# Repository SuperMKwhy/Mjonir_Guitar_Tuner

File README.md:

# Mjonir — Automatic Guitar Tuner

A handheld automatic guitar tuner built on an ESP32. A MEMS microphone listens to
the plucked string, an FFT finds its pitch, and a DC motor turns the tuning peg
until the string is in tune. An SSD1306 OLED and a 4-button D-pad provide the UI.

> **Status: work in progress.** The hardware is still being developed, so the
> firmware is incomplete and has not been fully tested on the final board.

## Features

- Pitch detection with a 2048-point FFT (ESP-DSP) on the INMP441 I2S microphone
- Motor drive through a DRV8833, with speed proportional to the tuning error
- Tuning presets: **Default** (E A D G B E), **All Flat** (Eb), and **Custom**
  (choose any note for each string)
- **Manual** mode (you pick the string) and **Auto** mode (detects the closest string)
- On-screen tuning meter showing the target note, its neighbours, and a ±2% in-tune window
- Battery level indicator

## Repository layout

```
firmware/   ESP-IDF project (C++)
  main/                 app entry point and page stack loop
  components/tunerLib/  I2S microphone driver, FIR filter + downsampling, FFT pitch detection
  components/control/   DRV8833 motor control (LEDC PWM)
  components/page/      UI pages: menu, tuning presets, custom tuning, tuner
  components/display/   SSD1306 helpers
  components/system/    D-pad input, cursor, battery ADC, note/frequency utilities
hardware/   KiCad 9 project: main PCB, D-pad PCB, BOM, PDFs, STEP models
cad/        Mechanical enclosure model (SolidWorks; to be added)
```

## Hardware

| Part | Notes |
|---|---|
| ESP32-WROOM-32 | Main MCU |
| INMP441 | I2S MEMS microphone |
| DRV8833 module | Motor driver for the peg winder |
| SSD1306 OLED 128×64 | I2C display |
| 4× tactile switch | D-pad on a separate PCB |
| YB-8 module, battery, power switch, buzzer | See `hardware/2. Project Tuner.csv` for the full BOM |

### Pin map

| Function | GPIO |
|---|---|
| OLED SDA / SCL | 21 / 22 |
| I2S WS / SCK / SD | 12 / 14 / 13 |
| Motor AIN1 / AIN2 | 18 / 19 |
| D-pad Up / Right (OK) / Down / Left (Back) | 25 / 26 / 32 / 33 |
| Battery sense (ADC1_CH7) | 35 |

## Building the firmware

Requires **ESP-IDF v5.1.x**. The `esp-dsp` and `ssd1306` components are
downloaded automatically by the IDF component manager.

```bash
. ~/esp/esp-idf/export.sh
cd firmware
idf.py set-target esp32   # first time only
idf.py build
idf.py -p /dev/ttyUSB0 flash monitor
```

> If you use Anaconda, its `python3` can conflict with ESP-IDF's Python
> environment. Put the system Python first: `export PATH=/usr/bin:$PATH` before
> sourcing `export.sh`.

## Controls

| Button | Action |
|---|---|
| Up / Down | Move the cursor, or change the value while editing |
| Right | OK / select |
| Left | Back / cancel |

## Known limitations / TODO

- Bass tuning is listed in the menu but not implemented yet
- Noise calibration is disabled (`calibration_time = 0`)
- Pitch resolution is about 1 Hz per FFT bin with no interpolation, which is coarse
  for low strings
- Uses legacy ESP-IDF I2S, ADC and SSD1306 drivers (deprecated in IDF 5.x)
- The buzzer is on the PCB but not used by the firmware yet
- Mechanical CAD model not yet in the repo

> ⚠️ When testing, keep the motor disconnected from the peg until you have
> confirmed the direction of rotation, so it cannot over-tighten a string.

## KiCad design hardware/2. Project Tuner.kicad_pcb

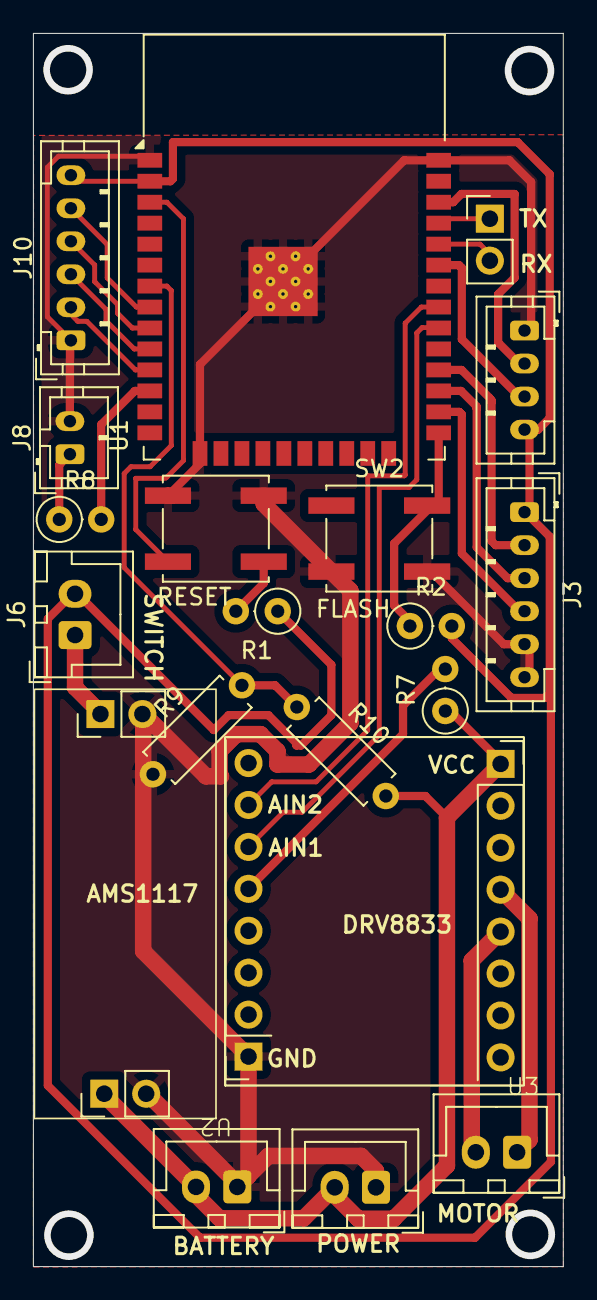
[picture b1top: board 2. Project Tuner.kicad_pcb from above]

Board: 2 copper layers, 32.1 x 74.7 mm, 20 parts (0 on the bottom side), 25 nets.

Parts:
J1: BATTERY; JST_XH_B2B-XH-A_1x02_P2.50mm_Vertical
J2: Flasher; PinHeader_1x02_P2.54mm_Vertical
J3: INMP441 Connection; JST_PH_B6B-PH-K_1x06_P2.00mm_Vertical
J4: POWER; JST_XH_B2B-XH-A_1x02_P2.50mm_Vertical
J5: Motor; JST_XH_B2B-XH-A_1x02_P2.50mm_Vertical
J6: ON/OFF Switch; JST_XH_B2B-XH-A_1x02_P2.50mm_Vertical
J7: ssd1306; JST_PH_B4B-PH-K_1x04_P2.00mm_Vertical
J8: Buzzer; JST_PH_B2B-PH-K_1x02_P2.00mm_Vertical
J10: D-Pad-Out; JST_PH_B6B-PH-K_1x06_P2.00mm_Vertical
R1, R2, R7: 10k; R_Axial_DIN0207_L6.3mm_D2.5mm_P2.54mm_Vertical
R8: 100; R_Axial_DIN0207_L6.3mm_D2.5mm_P2.54mm_Vertical
R9: 10k; R_Axial_DIN0207_L6.3mm_D2.5mm_P7.62mm_Horizontal
R10: 20k; R_Axial_DIN0207_L6.3mm_D2.5mm_P7.62mm_Horizontal
RESET: RESET; SW_Push_1P1T_NO_CK_KSC6xxJ
SW2: FLASH; SW_Push_1P1T_NO_CK_KSC6xxJ
U1: ESP32-WROOM-32
U2: YB-8
U3: DRV8833 Module

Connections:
/AIN1: U1.30 (IO18), U3.6 (BO2)
/AIN2: U1.31 (IO19), U3.7 (BO1)
/AO1: J5.1, U3.4 (AO1)
/AO2: J5.2, U3.5 (AO2)
/Buzzer: R8.2, U1.12 (IO27)
/DOWN-Board: J10.5, U1.8 (IO32)
/LEFT-Board: J10.4, U1.9 (IO33)
/PERCENT: R9.2, R10.1, U1.7 (IO35)
/RIGHT-Board: J10.2, U1.11 (IO26)
/RX_Socket: J2.2, U1.34 (RXD0/IO3)
/SCK: J3.4, U1.26 (IO4)
/SCL: J7.2, U1.36 (IO22)
/SD: J3.2, U1.28 (IO17)
/SDA: J7.3, U1.33 (IO21)
/STBY: R7.2, U3.5 (AO2)
/TX_Socket: J2.1, U1.35 (TXD0/IO1)
/UP-Board: J10.3, U1.10 (IO25)
/V_PRE: J6.1, U2.1 (V_IN)
/WS: J3.3, U1.27 (IO16)
GND: J1.1, J3.5, J3.6, J4.1, J7.1, J8.2, J10.1, R9.1, RESET.1, SW2.1, U1.1 (GND), U1.15 (GND), U1.38 (GND), U1.39 (GND), U2.2 (GND), U3.1 (VM)
unnamed: J8.1, R8.1
unnamed: R1.2, RESET.2, U1.3 (EN)
unnamed: R2.1, SW2.2, U1.25 (IO0)
VCC: J1.2, J4.2, R7.1, R10.2, U2.1 (V_IN), U3.1 (VM)
VDD: J3.1, J6.2, J7.4, J10.6, R1.1, R2.2, U1.2 (VDD)

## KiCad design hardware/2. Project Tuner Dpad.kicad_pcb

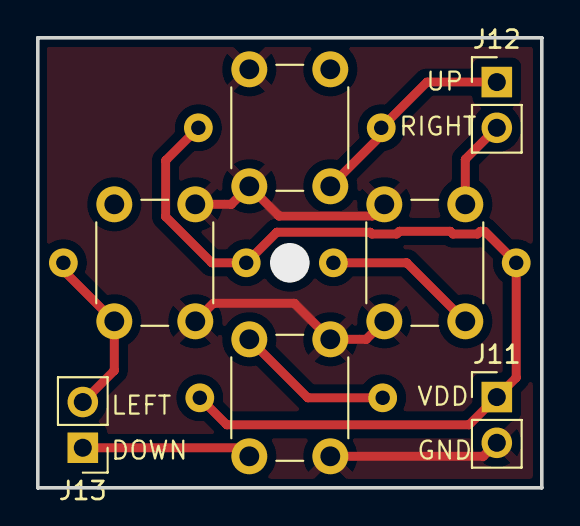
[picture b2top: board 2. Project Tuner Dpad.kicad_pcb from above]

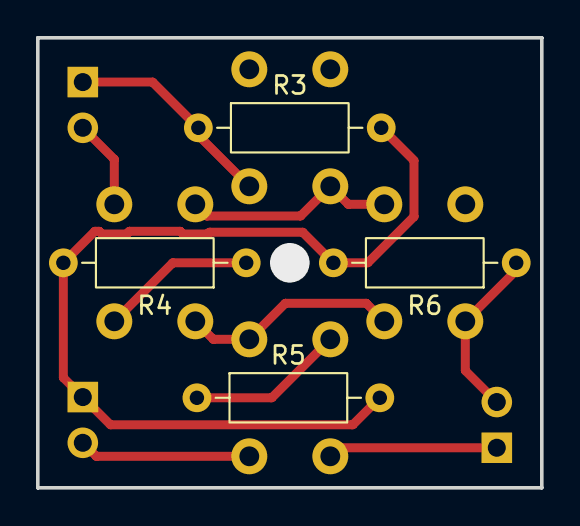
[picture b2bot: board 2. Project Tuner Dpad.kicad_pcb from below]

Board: 2 copper layers, 28.0 x 25.0 mm, 11 parts (4 on the bottom side), 6 nets.

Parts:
J11: D-Pad-PWR; PinHeader_1x02_P2.54mm_Vertical
J12: D-Pad-UR; PinHeader_1x02_P2.54mm_Vertical
J13: D-Pad-LD; PinHeader_1x02_P2.54mm_Vertical
R3, R4, R5, R6: 10k; R_Axial_DIN0207_L6.3mm_D2.5mm_P10.16mm_Horizontal
SW3: UP; SW_PUSH_6mm_H7.3mm
SW4: RIGHT; SW_PUSH_6mm_H7.3mm
SW5: DOWN; SW_PUSH_6mm_H7.3mm
SW6: LEFT; SW_PUSH_6mm_H7.3mm

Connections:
/DOWN: J13.1, R5.1, SW5.1
/GND-D-Pad: J11.2, SW3.2, SW4.2, SW5.2, SW6.2
/LEFT: J13.2, R6.1, SW6.1
/RIGHT: J12.2, R4.1, SW4.1
/UP: J12.1, R3.1, SW3.1
/VDD-D-Pad: J11.1, R3.2, R4.2, R5.2, R6.2

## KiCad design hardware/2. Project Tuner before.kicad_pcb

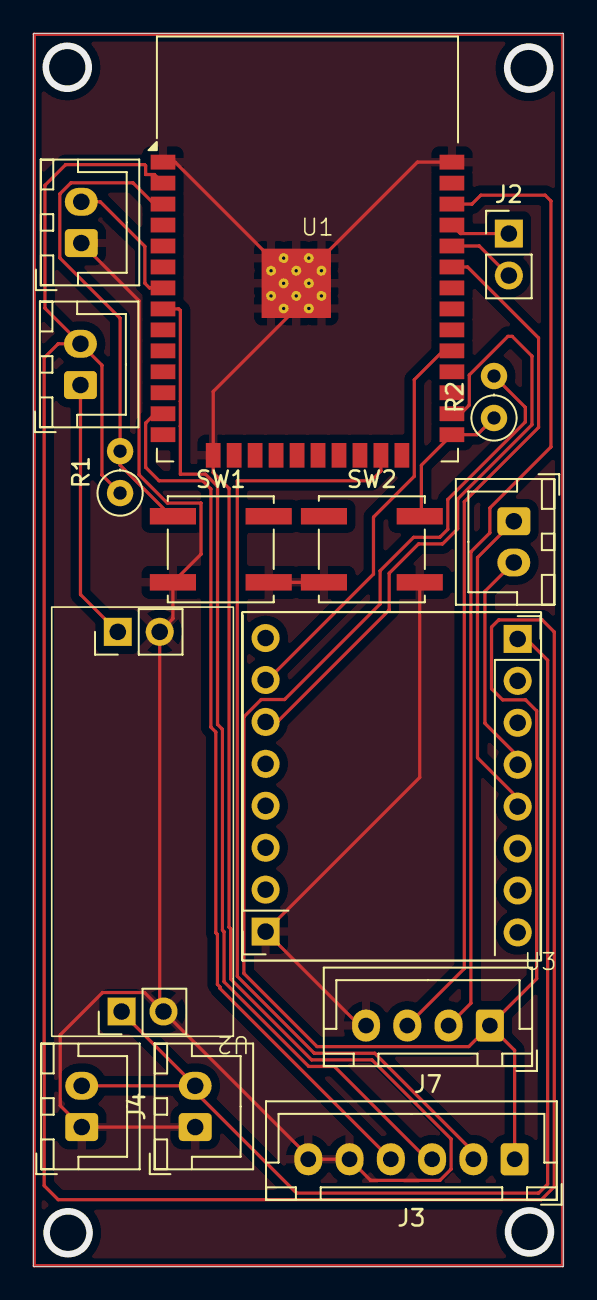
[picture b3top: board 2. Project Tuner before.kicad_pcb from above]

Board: 2 copper layers, 32.1 x 74.7 mm, 15 parts (0 on the bottom side), 16 nets.

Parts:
J1: BATTERY; JST_XH_B2B-XH-A_1x02_P2.50mm_Vertical
J2: Flasher; PinHeader_1x02_P2.54mm_Vertical
J3: INMP441 Connection; JST_XH_B6B-XH-A_1x06_P2.50mm_Vertical
J4: POWER; JST_XH_B2B-XH-A_1x02_P2.50mm_Vertical
J5: Motor; JST_XH_B2B-XH-A_1x02_P2.50mm_Vertical
J6: ON/OFF Switch; JST_XH_B2B-XH-A_1x02_P2.50mm_Vertical
J7: ssd1306; JST_XH_B4B-XH-A_1x04_P2.50mm_Vertical
J8: Buzzer; JST_XH_B2B-XH-A_1x02_P2.50mm_Vertical
R1, R2: 10k; R_Axial_DIN0207_L6.3mm_D2.5mm_P2.54mm_Vertical
SW1: RESET; SW_Push_1P1T_NO_CK_KSC6xxJ
SW2: FLASH; SW_Push_1P1T_NO_CK_KSC6xxJ
U1: ESP32-WROOM-32; ESP-WROOM-32 Edited
U2: YB-8
U3: DRV8833 Module

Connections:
/AIN2: U1.29 (IO5), U3.7 (BO1)
/RX_Socket: J2.2, U1.34 (RXD0/IO3)
/SCK: J3.4, U1.13 (IO14)
/SCL: J7.2, U1.36 (IO22)
/SD: J3.3, U1.8 (IO32)
/SDA: J7.3, U1.33 (IO21)
/TX_Socket: J2.1, U1.35 (TXD0/IO1)
/WS: J3.2, U1.23 (IO15)
GND: J1.1, J3.5, J3.6, J4.1, J7.4, J8.1, SW1.1, SW2.1, U1.1 (GND), U1.15 (GND), U1.38 (GND), U1.39 (GND), U2.2 (GND), U3.1 (VM)
unnamed: J5.1, U3.5 (AO2)
unnamed: J5.2, U3.4 (AO1)
unnamed: J8.2, U1.7 (IO35)
unnamed: R1.2, SW1.2, U1.3 (EN)
unnamed: R2.1, SW2.2, U1.25 (IO0)
VCC: J1.2, J4.2, U2.1 (V_IN), U3.1 (VM)
VDD: J3.1, J6.1, J6.2, J7.1, R1.1, R2.2, U1.2 (VDD), U2.1 (V_IN)
